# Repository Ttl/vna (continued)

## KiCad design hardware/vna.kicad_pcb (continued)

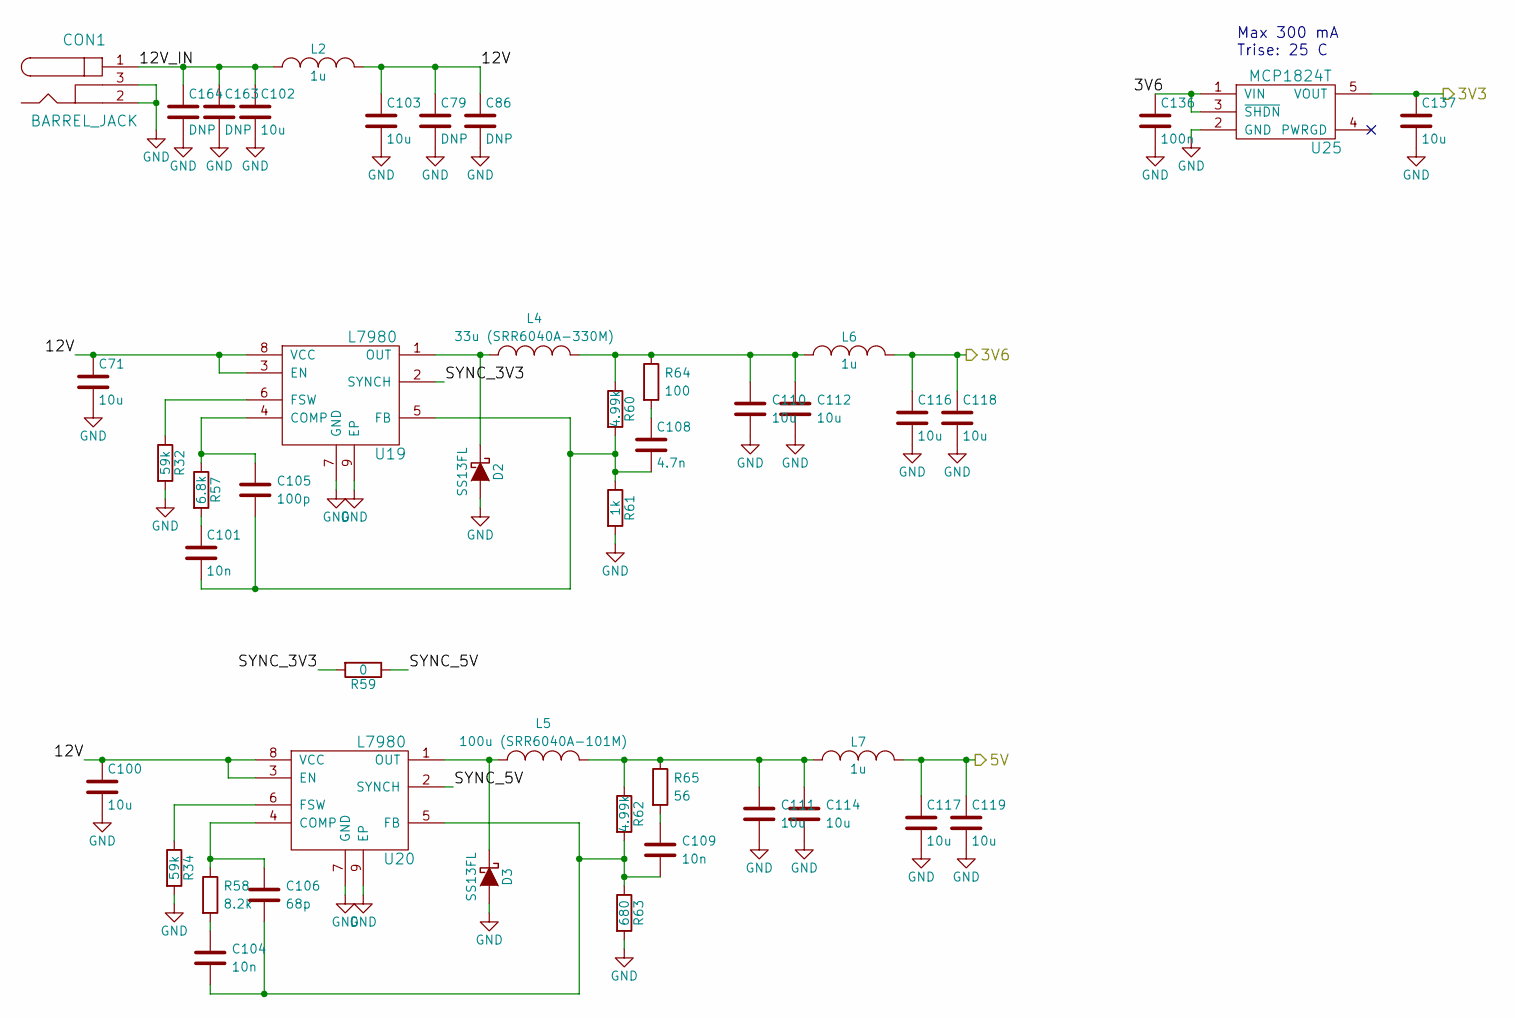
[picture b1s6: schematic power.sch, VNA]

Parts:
C71, C100, C102, C103, C110, C111, C112, C114, C116, C117, C118, C119, C137: 10u; C_0805b
C79, C86, C163, C164: DNP; C_0805b
C101, C104, C109: 10n; C_0402b
C105: 100p; C_0402b
C106: 68p; C_0402b
C108: 4.7n; C_0402b
C136: 100n; C_0402b
CON1: BARREL_JACK; EJ508A
D2, D3: SS13FL; SOD-123F
L2, L6, L7: 1u; C_0805b
L4: 33u (SRR6040A-330M); SRR6040A
L5: 100u (SRR6040A-101M); SRR6040A
R32, R34: 59k; R_0402b
R57: 6.8k; R_0402b
R58: 8.2k; R_0402b
R59: 0; R_0402b
R60, R62: 4.99k; R_0402b
R61: 1k; R_0402b
R63: 680; R_0402b
R64: 100; R_0402b
R65: 56; R_0402b
U19, U20: L7980; DFN-8-1EP_3x3mm_Pitch0.5mm
U25: MCP1824T; SOT-23-5

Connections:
/microcontroller/3V3: C137.1, U25.5 (VOUT); also elsewhere on the board
/power/3V6: C116.1, C118.1, C136.1, L6.2, U25.1 (VIN), U25.3 (~SHDN); also elsewhere on the board
/power/5V: C117.1, C119.1, L7.2; also elsewhere on the board
/power/12V: C71.1, C79.1, C86.1, C100.1, C103.1, L2.2, U19.3 (EN), U19.8 (VCC), U20.3 (EN), U20.8 (VCC)
/power/12V_IN: C102.1, C163.1, C164.1, CON1.1, L2.1
/power/SYNC_3V3: R59.2, U19.2 (SYNCH)
/power/SYNC_5V: R59.1, U20.2 (SYNCH)
GND: C71.2, C79.2, C86.2, C100.2, C102.2, C103.2, C110.2, C111.2, C112.2, C114.2, C116.2, C117.2, C118.2, C119.2, C136.2, C137.2, C163.2, C164.2, CON1.2, CON1.3, D2.2 (A), D3.2 (A), R32.2, R34.2, R61.2, R63.2, U19.7 (GND), U19.9 (EP), U20.7 (GND), U20.9 (EP), U25.2 (GND); also elsewhere on the board
unnamed: C101.1, R57.2
unnamed: C101.2, C105.2, C108.2, R60.2, R61.1, U19.5 (FB)
unnamed: C104.1, R58.2
unnamed: C104.2, C106.2, C109.2, R62.2, R63.1, U20.5 (FB)
unnamed: C105.1, R57.1, U19.4 (COMP)
unnamed: C106.1, R58.1, U20.4 (COMP)
unnamed: C108.1, R64.2
unnamed: C109.1, R65.2
unnamed: C110.1, C112.1, L4.2, L6.1, R60.1, R64.1
unnamed: C111.1, C114.1, L5.2, L7.1, R62.1, R65.1
unnamed: D2.1 (K), L4.1, U19.1 (OUT)
unnamed: D3.1 (K), L5.1, U20.1 (OUT)
unnamed: R32.1, U19.6 (FSW)
unnamed: R34.1, U20.6 (FSW)

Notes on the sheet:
Max 300 mA Trise: 25 C

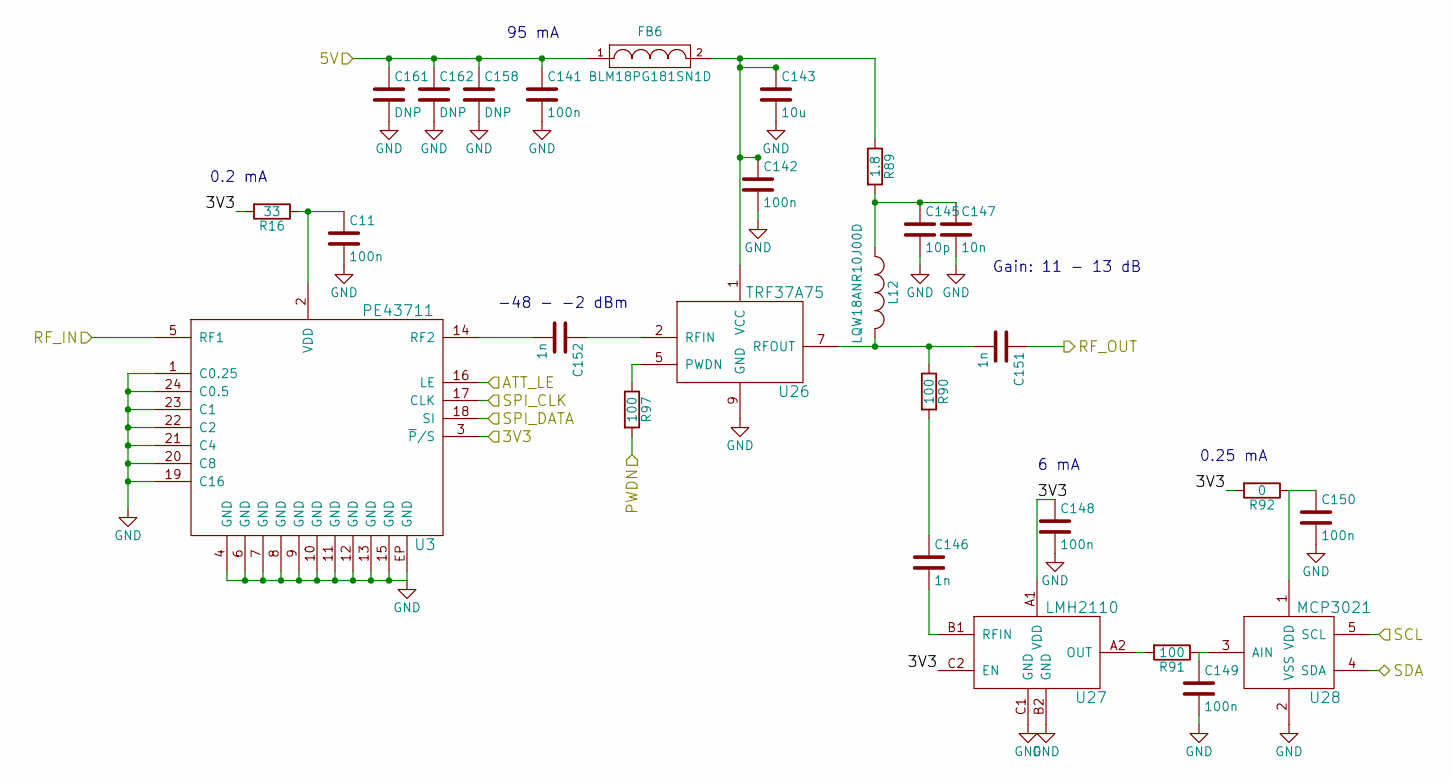
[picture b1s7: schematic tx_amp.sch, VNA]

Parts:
C11, C141, C142, C148, C149, C150: 100n; C_0402b
C143: 10u; C_0805b
C145: 10p; C_0402b
C146, C151, C152: 1n; C_0402b
C147: 10n; C_0402b
C158: DNP; C_0805b
C161, C162: DNP; C_0402b
FB6: BLM18PG181SN1D; C_0603b
L12: LQW18ANR10J00D; C_0603b
R16: 33; R_0402b
R89: 1.8; R_0603b
R90, R91, R97: 100; R_0402b
R92: 0; R_0402b
U3: PE43711; VQFN-24
U26: TRF37A75; DFN-8-1EP_2x2mm_Pitch0.5mm
U27: LMH2110; WFBGA-6
U28: MCP3021; SOT-23-5

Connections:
/microcontroller/3V3: C148.1, R16.2, R92.2, U3.3 (~P~/S), U27.A1 (VDD), U27.C2 (EN); also elsewhere on the board
/microcontroller/ATT_LE: U3.16 (LE); also elsewhere on the board
/microcontroller/I2C_SCL: U28.5 (SCL); also elsewhere on the board
/microcontroller/I2C_SDA: U28.4 (SDA); also elsewhere on the board
/microcontroller/PWDN: R97.2; also elsewhere on the board
/power/5V: C141.1, C158.1, C161.1, C162.1, FB6.1; also elsewhere on the board
/receiver/CLK: U3.17 (CLK); also elsewhere on the board
/receiver/DATA: U3.18 (SI); also elsewhere on the board
/tx_amp/RF_IN: U3.5 (RF1); also elsewhere on the board
/tx_amp/RF_OUT: C151.1; also elsewhere on the board
GND: C11.2, C141.2, C142.2, C143.2, C145.2, C147.2, C148.2, C149.2, C150.2, C158.2, C161.2, C162.2, U3.1 (C0.25), U3.4 (GND), U3.6 (GND), U3.7 (GND), U3.8 (GND), U3.9 (GND), U3.10 (GND), U3.11 (GND), U3.12 (GND), U3.13 (GND), U3.15 (GND), U3.19 (C16), U3.20 (C8), U3.21 (C4), U3.22 (C2), U3.23 (C1), U3.24 (C0.5), U3.EP (GND), U26.9 (GND), U27.B2 (GND), U27.C1 (GND), U28.2 (VSS); also elsewhere on the board
unnamed: C11.1, R16.1, U3.2 (VDD)
unnamed: C142.1, C143.1, FB6.2, R89.1, U26.1 (VCC)
unnamed: C145.1, C147.1, L12.1, R89.2
unnamed: C146.1, R90.2
unnamed: C146.2, U27.B1 (RFIN)
unnamed: C149.1, R91.1, U28.3 (AIN)
unnamed: C150.1, R92.1, U28.1 (VDD)
unnamed: C151.2, L12.2, R90.1, U26.7 (RFOUT)
unnamed: C152.1, U26.2 (RFIN)
unnamed: C152.2, U3.14 (RF2)
unnamed: R91.2, U27.A2 (OUT)
unnamed: R97.1, U26.5 (PWDN)

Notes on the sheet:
-48 - -2 dBm
Gain: 11 - 13 dB
6 mA
0.25 mA
95 mA
0.2 mA

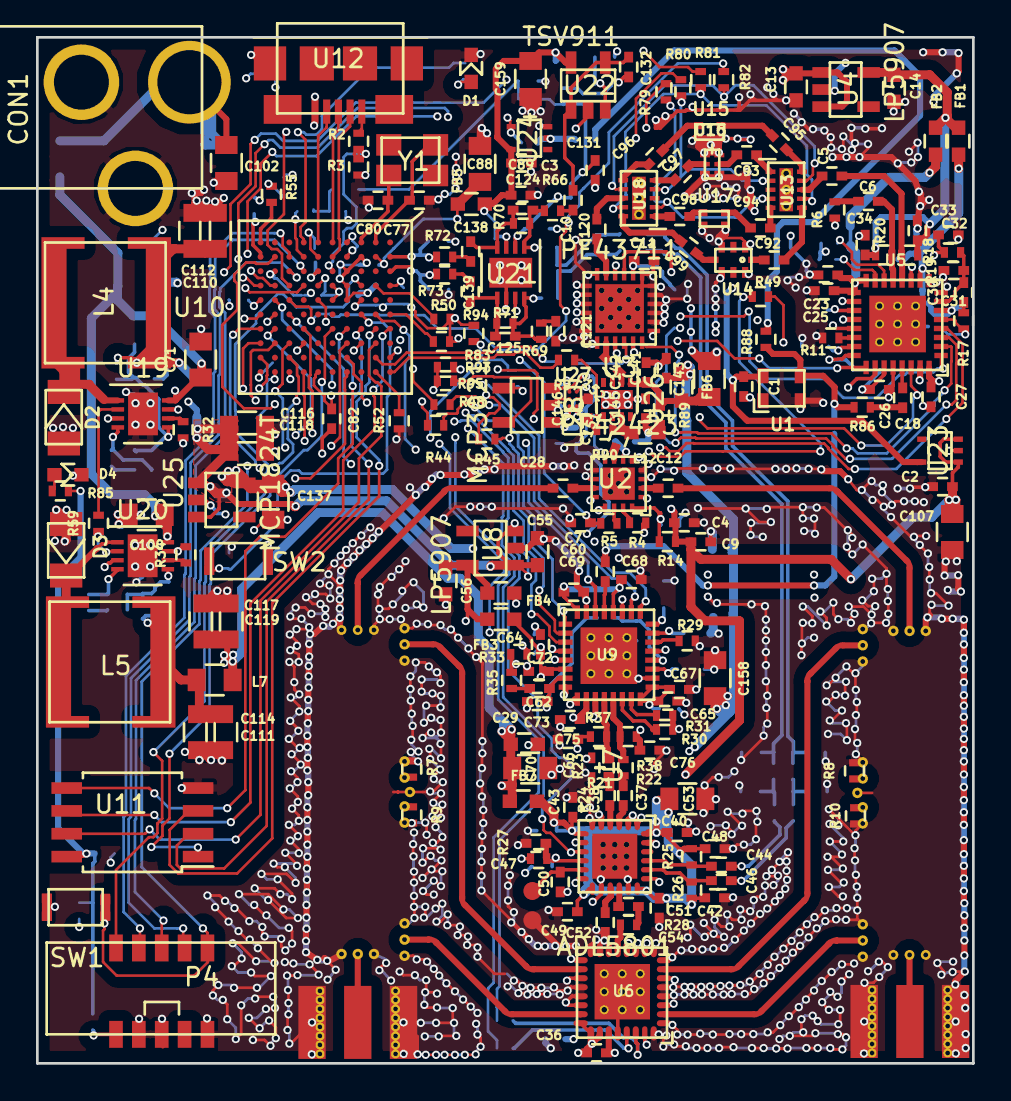
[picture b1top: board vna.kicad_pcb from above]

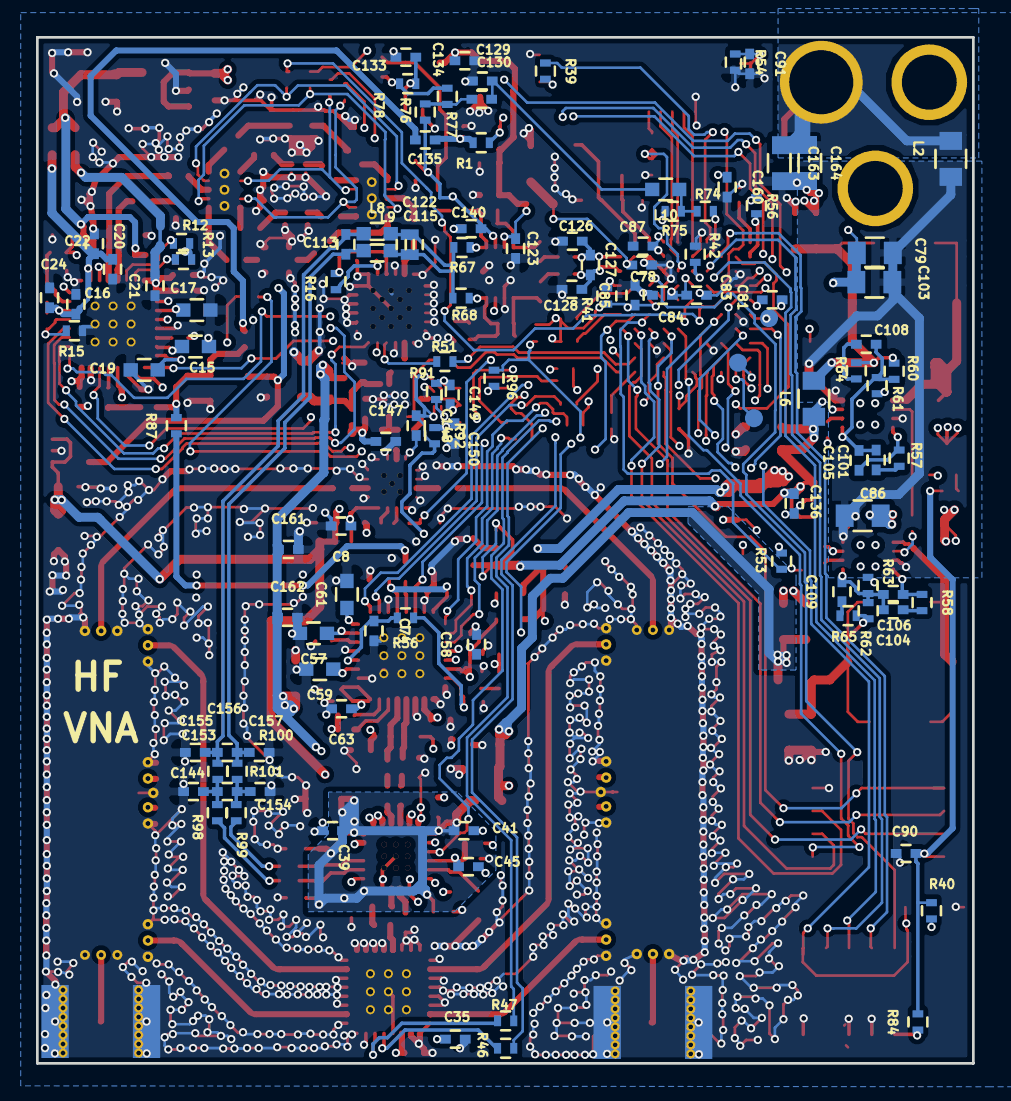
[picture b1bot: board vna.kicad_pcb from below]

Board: 4 copper layers, 52.0 x 57.0 mm, 342 parts (113 on the bottom side), 237 nets.

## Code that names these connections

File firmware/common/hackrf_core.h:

/*
 * Copyright 2012 Michael Ossmann <mike@ossmann.com>
 * Copyright 2012 Benjamin Vernoux <titanmkd@gmail.com>
 * Copyright 2012 Jared Boone <jared@sharebrained.com>
 *
 * This file is part of HackRF.
 *
 * This program is free software; you can redistribute it and/or modify
 * it under the terms of the GNU General Public License as published by
 * the Free Software Foundation; either version 2, or (at your option)
 * any later version.
 *
 * This program is distributed in the hope that it will be useful,
 * but WITHOUT ANY WARRANTY; without even the implied warranty of
 * MERCHANTABILITY or FITNESS FOR A PARTICULAR PURPOSE.  See the
 * GNU General Public License for more details.
 *
 * You should have received a copy of the GNU General Public License
 * along with this program; see the file COPYING.  If not, write to
 * the Free Software Foundation, Inc., 51 Franklin Street,
 * Boston, MA 02110-1301, USA.
 */

#ifndef __HACKRF_CORE_H
#define __HACKRF_CORE_H

#ifdef __cplusplus
extern "C"
{
#endif

#include <stdint.h>
#include <stdbool.h>

#define BOARD_ID 2

/*
 * SCU PinMux
 */

/* GPIO Output PinMux */

#define SCU_PINMUX_LED1     (P0_1) /* GPIO0[1] on P0_1 */

#define SCU_PINMUX_DITHER   (P0_0)
#define SCU_PINMUX_FILTER1  (P1_5)
#define SCU_PINMUX_FILTER2  (P1_6)
#define SCU_PINMUX_FILTER3  (P1_7)
#define SCU_PINMUX_FILTER4  (P1_8)
#define SCU_PINMUX_LO_LD    (P1_9)
#define SCU_PINMUX_SOURCE_LD    (P1_10)
#define SCU_PINMUX_SOURCE_LE    (P1_11)
#define SCU_PINMUX_SOURCE_CE    (P1_12)
#define SCU_PINMUX_LO_CE    (P1_13)
#define SCU_PINMUX_LO_LE    (P1_14)
#define SCU_PINMUX_RX_MIX_ENBL    (P1_15)
#define SCU_PINMUX_LO_MUXOUT    (P1_16)
#define SCU_PINMUX_SOURCE_MUXOUT    (P1_17)
#define SCU_PINMUX_RX_V1    (P2_0)
#define SCU_PINMUX_RX_V2    (P2_1)
#define SCU_PINMUX_LO_RF_ENABLE    (P2_2)
#define SCU_PINMUX_I2C_SDA    (P2_3)
#define SCU_PINMUX_I2C_SCL    (P2_4)
#define SCU_PINMUX_SOURCE_RF_ENABLE    (P2_5)
#define SCU_PINMUX_TX_SW_CTRL   (P2_11)
#define SCU_PINMUX_ATT_LE   (P2_12)
#define SCU_PINMUX_PWDN   (P2_13)
#define SCU_PINMUX_GP_CLKIN   (PF_4)

/* GPIO Input PinMux */
#define SCU_PINMUX_BOOT0    (P1_1)  /* GPIO0[8] on P1_1 */
#define SCU_PINMUX_BOOT1    (P1_2)  /* GPIO0[9] on P1_2 */
#define SCU_PINMUX_BOOT2    (P2_8)  /* GPIO5[7] on P2_8 */
#define SCU_PINMUX_BOOT3    (P2_9)  /* GPIO1[10] on P2_9 */

/* SSP1 Peripheral PinMux */
#define SCU_SSP1_MISO       (P1_3)  /* P1_3 */
#define SCU_SSP1_MOSI       (P1_4)  /* P1_4 */
#define SCU_SSP1_SCK        (P1_19) /* P1_19 */

/* SGPIO interface */
#define SCU_PINMUX_SGPIO0   (P0_0) /* D2 */
#define SCU_PINMUX_SGPIO1   (P0_1) /* D3 */
#define SCU_PINMUX_SGPIO2   (P1_15) /* D4 */
#define SCU_PINMUX_SGPIO3   (P1_16) /* D5 */
#define SCU_PINMUX_SGPIO4   (P2_0) /* D6 */
#define SCU_PINMUX_SGPIO5   (P2_1) /* D7 */
#define SCU_PINMUX_SGPIO6   (P2_2) /* D8 */
#define SCU_PINMUX_SGPIO7   (P1_0) /* D8 */
#define SCU_PINMUX_SGPIO8   (P1_12) /* CLK */
#define SCU_PINMUX_SGPIO9   (P1_13) /* CLK */
#define SCU_PINMUX_SGPIO10  (P1_14) /* D0 */
#define SCU_PINMUX_SGPIO11  (P1_17) /* D1 */

#define SCU_PINMUX_SGPIO12  (P1_18) /* NC */
#define SCU_PINMUX_SGPIO13  (P4_8) /* NC */
#define SCU_PINMUX_SGPIO14  (P1_6) /* NC */
#define SCU_PINMUX_SGPIO15  (P1_5) /* NC */

/* SPI flash */
#define SCU_SSP0_MISO       (P3_6)
#define SCU_SSP0_MOSI       (P3_7)
#define SCU_SSP0_SCK        (P3_3)
#define SCU_SSP0_SSEL       (P3_8) /* GPIO5[11] on P3_8 */
#define SCU_FLASH_HOLD      (P3_4) /* GPIO1[14] on P3_4 */
#define SCU_FLASH_WP        (P3_5) /* GPIO1[15] on P3_5 */

/*
 * GPIO Pins
 */

/* GPIO Output */
#define PIN_DITHER  (BIT0)
#define PORT_DITHER (GPIO0)

#define PIN_LED1    (BIT1)
#define PORT_LED1_3 (GPIO0)

#define PIN_FILTER1 (BIT8)
#define PORT_FILTER1 (GPIO1)

#define PIN_FILTER2 (BIT9)
#define PORT_FILTER2 (GPIO1)

#define PIN_FILTER3 (BIT0)
#define PORT_FILTER3 (GPIO1)

#define PIN_FILTER4 (BIT1)
#define PORT_FILTER4 (GPIO1)

#define PIN_LO_LD   (BIT2)
#define PORT_LO_LD  (GPIO1)

#define PIN_SOURCE_LD   (BIT3)
#define PORT_SOURCE_LD  (GPIO1)

#define PIN_SOURCE_LE   (BIT4)
#define PORT_SOURCE_LE  (GPIO1)

#define PIN_SOURCE_CE   (BIT5)
#define PORT_SOURCE_CE  (GPIO1)

#define PIN_LO_CE   (BIT6)
#define PORT_LO_CE  (GPIO1)

#define PIN_LO_LE   (BIT7)
#define PORT_LO_LE  (GPIO1)

#define PIN_RX_MIX_ENBL  (BIT2)
#define PORT_RX_MIX_ENBL  (GPIO0)

#define PIN_LO_MUXOUT  (BIT3)
#define PORT_LO_MUXOUT  (GPIO0)

#define PIN_SOURCE_MUXOUT  (BIT12)
#define PORT_SOURCE_MUXOUT  (GPIO0)

#define PIN_RX_V1  (BIT0)
#define PORT_RX_V1  (GPIO5)

#define PIN_RX_V2  (BIT1)
#define PORT_RX_V2  (GPIO5)

#define PIN_LO_RF_ENABLE  (BIT2)
#define PORT_LO_RF_ENABLE  (GPIO5)

#define PIN_SOURCE_RF_ENABLE  (BIT5)
#define PORT_SOURCE_RF_ENABLE  (GPIO5)

#define PIN_TX_SW_CTRL  (BIT11)
#define PORT_TX_SW_CTRL  (GPIO1)

#define PIN_ATT_LE  (BIT12)
#define PORT_ATT_LE  (GPIO1)

#define PIN_PWDN  (BIT13)
#define PORT_PWDN  (GPIO1)

#define PIN_FLASH_HOLD (BIT14) /* GPIO1[14] on P3_4 */
#define PIN_FLASH_WP   (BIT15) /* GPIO1[15] on P3_5 */
#define PORT_FLASH     (GPIO1)
#define PIN_SSP0_SSEL  (BIT11) /* GPIO5[11] on P3_8 */
#define PORT_SSP0_SSEL (GPIO5)

/* GPIO Input */
#define PIN_BOOT0   (BIT8)  /* GPIO0[8] on P1_1 */
#define PIN_BOOT1   (BIT9)  /* GPIO0[9] on P1_2 */
#define PIN_BOOT2   (BIT7)  /* GPIO5[7] on P2_8 */
#define PIN_BOOT3   (BIT10) /* GPIO1[10] on P2_9 */

/* Read GPIO Pin */
#define GPIO_STATE(port, pin) ((GPIO_PIN(port) & (pin)) == (pin))
#define BOOT0_STATE       GPIO_STATE(GPIO0, PIN_BOOT0)
#define BOOT1_STATE       GPIO_STATE(GPIO0, PIN_BOOT1)
#define BOOT2_STATE       GPIO_STATE(GPIO5, PIN_BOOT2)
#define BOOT3_STATE       GPIO_STATE(GPIO1, PIN_BOOT3)

typedef enum {
	TRANSCEIVER_MODE_OFF = 0,
	TRANSCEIVER_MODE_RX = 1,
	TRANSCEIVER_MODE_TX = 2
} transceiver_mode_t;

void delay(uint32_t duration);

void cpu_clock_init(void);
void cpu_clock_pll1_low_speed(void);
void cpu_clock_pll1_max_speed(void);
void ssp1_init(void);
void ssp1_set_mode_16bit(void);
void ssp1_set_mode_8bit(void);

void pin_setup(void);

#ifdef HACKRF_ONE
void enable_rf_power(void);
void disable_rf_power(void);
#endif

#ifdef __cplusplus
}
#endif

#endif /* __HACKRF_CORE_H */

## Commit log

2016-06-19 Add source power detector readout
2016-07-21 Configure ADCHS
2016-07-27 Add hardware design files
2016-07-29 Update firmware
2016-08-02 Add processing software
2016-08-02 Add missing firmware files
2016-08-02 Simple readme
2016-08-02 Add pdf of schematic
2016-08-10 Wait for PLLs to lock, better DMA setup
    Cleaning
2016-08-10 Update PC program
    Changes in firmware
    Add option to do more averaging at low frequencies
    Don't calculate LO signals all the time
2016-08-11 Fix 1-port channel sampling lengths
    Lengths changed when the firmware was changed.
2016-08-13 Add ADC dithering
    Replaced delay loop in sampling with timer
2016-08-13 Change channel lengths
    Modified again due to firmware changes
2016-08-14 Configurable channel sampling
    Channels to be sampled and their sampling times
    can now be configured with PC.
2016-08-15 Automatically determine channel boundaries in sampled data
2016-08-18 Frequency offset estimation with Kalman filter
    Estimates the on-board oscillator frequency offset from RX channel
    measurement.
    Currently very slow and probably not necessary to do at every frequency point
    Also averaged IQ sample is now calculated right after the measurement
    by normalizing phase of the RX channel to 0.
2016-12-10 Bug fixes
    Fix missing and wrong sized PLL register definitions.
    Fix the digital LO frequency and remove the unneeded frequency
    offset estimation.
2017-08-17 Add power calibration file
